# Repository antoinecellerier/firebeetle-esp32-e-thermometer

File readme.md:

A low power ESP32 based thermometer with an ePaper display

| Prototype | Custom board |
|-----------|--------------|
|||

See [docs/wiring.md](docs/wiring.md) for prototype wiring information and [hardware/thermometer-c6/](hardware/thermometer-c6/README.md) for the custom board. More pictures [lower down](#prototypes-in-action).

# Power consumption

Measured with a Nordic PPK2 on pure ESP-IDF firmware; full traces, dates and
methodology in [docs/notes.md](docs/notes.md). Figures are config-specific —
panel, sensor and board all matter.

**Read the node tag on every figure.** `@3V3 rail` is the load alone, with the
board's input tree bypassed; `@4V2 bat` is the whole deployment path, regulator
and charger leakage included. They are not interchangeable, and the battery
figure is not simply the larger one.

| Setup | Deep-sleep floor | Sensor wake | Wake + refresh |
|-------|-----------------|-------------|----------------|
| Firebeetle ESP32-E + BMP390L + GDEH0154Z90 via DESPI-C02 (FDN340P gate) | 19–20 µA `@3V3 rail` | ULP bit-bang I2C every 5 s, avg ≈0 | ~112 mC `@3V3 rail` (was ~600 mC before light sleep — the Z90's ~21 s refresh used to spin-wait) |
| XIAO ESP32-C6 + BMP581 + GDEH0576T81 via DESPI-C02 (FDN340P gate) | 15.5–16 µA `@3V3 rail` | LP core I2C every 60 s: ~1 mA × 3 ms | ~45 mC `@3V3 rail` — **superseded, re-measure** (see below) |
| XIAO ESP32-C6 + BMP581 + GDEW029I6FD via Seeed ePaper Driver Board (no gate) | ~25 µA `@3V3 rail`<br>**21.7 µA `@4V2 bat`** | LP core I2C every 60 s: ~1 mA × 3 ms | 12.2 mC `@3V3 rail`<br>**10.05 mC `@4V2 bat`** |
| thermometer-c6 rev A + BMP581 + GDEM0154I61 (on-board gated booster) | **18.3 µA `@4V2 bat`** | LP core I2C every 60 s | **~24.3 mC `@4V2 bat`** |
| thermometer-c6 rev A + BMP581 + GDEH0576T81 (on-board gated booster) | **19.05 µA `@4V2 bat`** | LP core I2C every 60 s | **36.77 mC `@4V2 bat`** |

The XIAO's GDEH0576T81 figure is **superseded**: it was taken while the panel ran
its coldest waveform LUT, which cost 48% of panel busy time. The last row is the
deployment configuration on the corrected waveform — daily budget and derivation
in [docs/notes.md](docs/notes.md).

A buck draws *less* current at 4.2 V than its load does at 3.3 V, which is why
~25 µA at the rail reads 21.7 µA at the battery (~90 % efficient). An LDO runs
the other way, ~1.15× the charge for the same work — so the custom board beating
the XIAO by 3 µA at the same 4.2 V is a real win, not a topology artefact. Its
wake figures include LED blinks, left on for observability. Blank cells are
unmeasured, not zero; both are on the PPK2 backlog.

The main CPU only wakes on a ≥0.1 °C delta or a safety-net tick, so a display
refresh is the dominant event on a typical day. At one refresh per hour that puts
long-term averages in the **~16–51 µA band depending on rig and refresh cadence**
— load-only runtime of roughly **1–3 years on a 400 mAh LiPo**, with the
deployment configuration measured at the bottom of that band (~2.3–3.8 C/day,
~380–620 days; derivation in [docs/notes.md](docs/notes.md)). But at this
current level LiPo self-discharge (a few %/month ≈ 15–25 µA equivalent) rivals
the load itself, so **expected runtime is on the order of a year**, and a
2600 mAh 18650 will age out before the load meaningfully drains it. Not yet
confirmed against a full-length run.

Two gotchas worth surfacing (the adapter-leakage ones are under Hardware below):
- **XIAO ESP32-C6 battery operation has a hard floor at ~3.6 V**: its 3.3 V rail is a pure buck (SGM6029C), which below VOUT + ~245 mV starves its bootstrap and lets the rail sag ~a VTH below VBAT — deep sleep survives, but wakes collapse into 0.5–0.9 A brownout-restart storms. Firmware shuts down at 3.7 V (~12–15 % of Li-ion capacity abandoned); full regime map in [docs/notes.md](docs/notes.md). LiFePO₄ cells (3.2 V nominal) are unusable on this board. The custom board uses an LDO and shuts down at 3.5 V instead.
- **Don't use the Seeed ePaper Driver Board's JST battery connector**: its ETA9740 charger/boost idles at ~330–500 µA — ~20× the whole system's sleep floor, flattening a 400 mAh cell in ~7 weeks doing nothing — and it double-converts BAT→5 V→3.3 V. Solder the battery to the XIAO's underside BAT pads instead, JST empty, switch off.

The Arduino-era ~20 mA deep-sleep USB CDC gotcha is gone: the pure-IDF
USB-Serial-JTAG console doesn't hold the port active.

For context: the original 2021 prototype (wake + refresh every 60 s, no ULP) ran a 2600 mAh cell flat in 8.5 days at ~12.6 mA average — the ULP/LP-core redesign is ~700× more efficient.

# Hardware

Looking to replicate this? Easy to start with options are tagged **[start with this]** below.

## Controller boards
- thermometer-c6 — the custom board this project builds towards, replacing the
  dev-board rigs below: ESP32-C6-MINI-1 + BMP581, a universal 24-pin FPC panel
  interface with the Good Display booster on-board and P-FET-gated, USB-C charging,
  an LDO 3.3 V rail, a GPIO-switched battery divider and a 32.768 kHz crystal.
  Schematic, PCB and rationale: [hardware/thermometer-c6/](hardware/thermometer-c6/README.md)
- Seeed Studio XIAO ESP32-C6 https://wiki.seeedstudio.com/xiao_esp32c6_getting_started/ **[start with this]**
- (Early 2021 prototype) Firebeetle ESP32-E https://wiki.dfrobot.com/FireBeetle_Board_ESP32_E_SKU_DFR0654
  - ESP32 datasheet https://www.espressif.com/sites/default/files/documentation/esp32_datasheet_en.pdf
  - ESP32-WROOM-32E datasheet  https://www.espressif.com/sites/default/files/documentation/esp32-wroom-32e_esp32-wroom-32ue_datasheet_en.pdf
  - TP4056 battery charger IC (onboard) https://dlnmh9ip6v2uc.cloudfront.net/datasheets/Prototyping/TP4056.pdf https://www.best-microcontroller-projects.com/tp4056.html

- ESP32 getting started https://docs.espressif.com/projects/esp-idf/en/latest/esp32/get-started/index.html
- ESP32 power consumption https://diyi0t.com/reduce-the-esp32-power-consumption/

## Temperature sensor (multiple options)
- BMP390L I2C interface:
  - datasheet https://www.bosch-sensortec.com/media/boschsensortec/downloads/datasheets/bst-bmp390-ds002.pdf
  - breakout board https://wiki.dfrobot.com/Fermion_BMP390L_Digital_Barometric_Pressure_Sensor_SKU_SEN0423
- BMP581 / BMP585 I2C interface (Bosch next-gen pressure sensors, ~0.5 µA deep-standby)
  - BMP581 https://www.bosch-sensortec.com/products/pressure-sensors/bmp581/
  - BMP585 https://www.bosch-sensortec.com/products/pressure-sensors/bmp585/
  - Fermion breakouts:
    - SEN0667 (BMP581) https://wiki.dfrobot.com/sen0667/ **[start with this]**
    - SEN0666 (BMP585) https://wiki.dfrobot.com/sen0666/
- (Early 2021 prototype) DS18B20-PAR OneWire interface
  - datasheet https://datasheets.maximintegrated.com/en/ds/DS18B20-PAR.pdf

## Display (multiple options)
- Good Display GDEW0154M09 black and white, 200x200, 1.54" fast full refresh https://www.good-display.com/product/206.html
- Good Display GDEW0213M21 black and white, 212x104, 2.13" DES screen https://www.good-display.com/product/354.html
- Good Display GDEW029I6FD black and white flex, 296x128, 2.9" (UC8151D, partial updates) https://www.good-display.com/product/209.html
- Good Display GDEM0154I61 black and white flex, 200x200, 1.54" (driven via GDEY0154D67 SSD1681 driver) https://www.good-display.com/product/535.html
- Good Display GDEH0576T81 black and white, 920x680, 5.76" HD (SSD2677, partial updates) https://www.good-display.com/product/702.html **[start with this]**
- (Early 2021 prototype) Adafruit 1.54" Tri-Color eInk / ePaper 200x200 Display with SRAM - SSD1681 Driver
https://www.adafruit.com/product/4868
https://learn.adafruit.com/adafruit-1-54-eink-display-breakouts?view=all
  - uses Good Display GDEH0154Z90 https://www.good-display.com/product/285.html

Good Display panels are driven through one of two adapters (same Good Display reference booster on both — panel compatibility notes in [docs/wiring.md](docs/wiring.md)):
- Good Display DESPI-C02 (switchable RESE 0.47/3 Ω) https://www.good-display.com/product/516.html
- Seeed ePaper Driver Board for XIAO (fixed RESE 0.47 Ω, ETA9740 charger — see gotcha above) https://www.seeedstudio.com/ePaper-breakout-Board-for-XIAO-V2-p-6374.html — wiki: https://wiki.seeedstudio.com/xiao_eink_expansion_board_v2/ **[start with this]**

The DESPI-C02's boost converter leaks ~534 µA in deep sleep, which an FDN340P P-channel MOSFET on the adapter's 3.3 V line eliminates; the Seeed board's ungated standby measured only ~9 µA, so it runs without a gate.

## Other components
- FDN340P P-channel MOSFET (SOT-23) — power-gates DESPI-C02 3.3 V during deep sleep
- AO3400A N-channel MOSFET (SOT-23) — switches the XIAO C6 battery voltage divider so it doesn't draw ~10 µA continuously

## Battery
- Current builds: PR502535 single-cell LiPo pouch, 400 mAh https://www.gotronic.fr/art-accu-lipo-3-7-vcc-400-mah-pr502535-5812.htm **[start with this or equivalent]**
- Original prototype: RS Pro 18650 26H Li-ion, 2600 mAh https://fr.rs-online.com/web/p/batteries-taille-speciale/1449406/

## Prototypes in action

### 2026 - ultra low power custom board

Custom rev A board (with BMP581), GDEM0154I61 & 400mAh battery

Custom rev A boards (with BMP581), GDEH0576T81 & 400mAh battery

### 2026 - ultra low power prototypes

Seed Xiao C6, BMP581, GDEH0576T81 & 400mAh battery

Seeed Xiao C6, e-Paper Driver Board, BMP581, GDEW029I6FD & 400mAh battery

Firebeetle ESP32-E, BMP390L, GDEH0154Z90 & 400mAh battery

### 2021 - first prototype
Firebeetle ESP32-E, DS18B20, GDEW0213M21 & 2600mAh battery

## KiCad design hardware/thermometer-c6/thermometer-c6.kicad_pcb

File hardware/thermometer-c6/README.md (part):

# thermometer-c6 — custom ultra-low-power e-paper thermometer board

Custom PCB replacing the XIAO-C6/FireBeetle dev-board rigs. ESP32-C6-MINI-1 +
BMP581 + universal 24-pin EPD interface with on-board gated booster, USB-C
charging, LDO power tree. Design driven by the PPK2 measurement campaign in
[`docs/notes.md`](../../docs/notes.md) (repo root).

**Status: rev A built and working.** Ordered 2026-07-20
([`archive/order-2026-07-20/`](archive/order-2026-07-20/); landed €273.93 ≈
€68.50/assembled board, breakdown in [`ORDERING.md`](ORDERING.md)). Board 1
passed bring-up Phases 0–2 on 2026-07-29 ([`BRINGUP.md`](BRINGUP.md)): first
render, LP-core survival, and a measured 18.3µA @ 4.2V deployment-path sleep
floor over a full field interval (docs/notes.md 2026-07-29) — vs 21.7µA at
the same 4.2V on the XIAO buck rig, validating the LDO tree. **Phase 3 is under
way on board 2, not board 1**: the GDEH0576T81 panels arrived 2026-08-11 and
board 2 took one plus a battery, so the phase is no longer gated on board 1
leaving its soak (still running since 2026-07-31; harvest before resetting it).
Closed on board 2 that day: the deployment configuration's power figures
(19.05µA floor, 36.77mC wake+refresh `@4V2 bat`), the boost rails under the
heaviest waveform the panel can be given (no sag — this is the evidence the
rev B bridge deletion was waiting on), the VBAT_ADC point (−24mV at 4.2V, 2mV
from board 1), the battery-floor sweep, and the WiFi resync charges. Board 2
went straight to flash on the strength of board 1's pass, worked first time,
and is both the bench board and now the Phase 3 vehicle; boards 3–4 are still
in the bag. The board is 48×35mm
2-layer, hand-routed, DRC-clean at full severity; fab export is `make fab`
(gerbers/drill + CPL/BOM zip, git-hash+date stamped, gated by
`verify/check_fab.py`); pre-order schematic sign-off (requirements proven
against primary sources, findings + dispositions):
[`SCHEMATIC-VERIFICATION.md`](SCHEMATIC-VERIFICATION.md).

## Why these choices (measurement rationale)

| Decision | Measurement behind it |
|---|---|
| LDO (not buck) 3.3V rail | XIAO's SGM6029C buck: razor-sharp dropout cliff at 3.545V → 0.5–0.9A brownout storms; forces 3.70V firmware shutdown, wasting ~12–15% of pack (notes.md 2026-07-05) |
| P-FET-gated EPD booster | DESPI-C02 leaks ~534µA with panel asleep; FDN340P gate mod → ~18µA (notes.md) |
| Switched 100k/100k battery divider | Always-on 200k divider ≈ 10µA (~⅔ of the sleep floor); 1M/1M biases the C6 SAR ADC low (~300ns sample window) (wiring.md) |
| High-side divider switch | Low-side switch leaves the sense node at VBAT through the top 100k → pin ESD diode clamps into 3V3 above ~3.7V (~5µA at 4.2V) |
| Load-sharing USB path | Without it, no-battery USB operation is limited to the 100mA charge current — EPD refresh peaks at ~465mA |
| Reverse-battery P-FET (Q6) | JST vs Adafruit pigtail polarity is a real supply-chain trap; MCP73831 abs-max is −0.3V — one AO3401A makes it survivable |
| EPD gate soft-start (R24/C28) | GPIO14 slamming Q2 on charge-shares 10µF against the rail faster than the LDO loop — ~100µs ramp kills the brownout risk |
| VBUS sense (R22/R23 → GPIO4) | Firmware needs to know USB is present: VBAT_ADC reads the charger CV node while charging, and SoC logic must ignore it; zero draw with USB absent |
| Jumper-selected inductor (JP5/JP6) | 10µH proven on all panels; 47µH per the GDEH0576T81 datasheet (with 2.2Ω RESE) — jumpers sit on the switch-node side so the unselected coil idles on the DC rail |
| 32.768kHz crystal | C6 on internal RC runs hours fast over weeks (memory: project_c6_clock_drift) |

## Reference transcription: DESPI-C02 V1.0 (Good Display, 2018-07-06)

Transcribed from `hardware/DESPI-C02_SCH V1.0.pdf` (visual + embedded netlist),
2026-07-07. This is the booster we replicate (with EPD_VCC gating added).

### 24-pin 0.5mm FPC panel pinout (P1, "FPC24(0.5MM)")

| Pin | Name | DESPI connection | Pin | Name | DESPI connection |
|---|---|---|---|---|---|
| 1 | NC | — | 13 | SCLK | host SPI SCK |
| 2 | GDR | Q1 gate + R1 10k→GND | 14 | SDI | host SPI MOSI |
| 3 | RESE | Q1 source + Rsense→GND | 15 | VDDIO | 3.3V |
| 4 | VGL | C1 4.7µF/25V→GND | 16 | VCI | 3.3V |
| 5 | VGH | C2 4.7µF/25V→GND | 17 | VSS | GND |
| 6 | TSCL | — (touch variant only) | 18 | VDD | C7 1µF/50V→GND |
| 7 | TSDA | — (touch variant only) | 19 | VPP | C8 1µF/50V→GND |
| 8 | BS | R4 3Ω→GND (= tied low, 4-wire SPI) | 20 | VSH | C9 4.7µF/25V→GND |
| 9 | BUSY | host | 21 | PREVGH | C5 4.7µF/25V→GND + D3 cathode |
| 10 | RES | host + R5 10k→3.3V pull-up | 22 | VSL | C10 4.7µF/25V→GND |
| 11 | D/C | host | 23 | PREVGL | C11 4.7µF/25V→GND + D1 anode |
| 12 | CS | host | 24 | VCOM | C12 1µF/50V→GND |

### Booster topology (all diodes MBR0530; orientation by function, not pin #)

- L1 10µH/1A: 3.3V → SW node
- Q1 Si1308EDL N-FET: gate=GDR (R1 10k bleed to GND), drain=SW, source=RESE
- RESE → Rsense → GND. DESPI: slide switch selects R3 0.47Ω or R2 3Ω.
  **This board: three parallel legs, each Rsense in series with a solder
  jumper: 0.47Ω (default-bridged) / 2.2Ω / 3Ω.**
- D3: anode=SW, cathode=PREVGH (boost rectifier)
- Negative charge pump: SW → C3 4.7µF/25V → X node; D2 anode=X, cathode=GND;
  D1 anode=PREVGL, cathode=X
- 3.3V rail bulk: C4 4.7µF/25V. (On this board the whole block hangs off the
  gated EPD_VCC rail, and the RES pull-up goes to EPD_VCC — never 3V3.)
- There are **no** PREVGH↔PREVGL/VCOM bridge caps in the real reference
  (the abandoned draft in `hardware/kicad/` invented them).

## ESP32-C6 pin map

| GPIO | Function | Notes |
|---|---|---|
| 0 / 1 | XTAL_32K_P / N | FC-135 32.768kHz + 20pF; R9 10M bias DNP — the C6's 32k oscillator amplifier runs at very low gm, so startup margin depends on crystal ESR spread (≤70kΩ allowed, rises when cold) and stray C; the parallel bias resistor (Espressif HDG checklist) gives the inverter a DC feedback path if a given board/batch won't start |
| 2 | VBAT_ADC (ADC1_CH2) | sense node of switched divider; 0V when divider off |
| 3 | VDIV_EN | 100k pull-down → divider hard-off in deep sleep |
| 4 | VBUS_SENSE (100k/100k from VBUS) | USB-presence detect; divider is dead (0V, zero drain) with USB unplugged |
| 5 | spare → J5 debug header | strap-adjacent (SDIO clock-edge only at default eFuses) — keep high-Z |
| 6 / 7 | LP I2C SDA / SCL | fixed by silicon; BMP581; 4.7k pull-ups to 3V3 |
| 8 | spare → J5 | STRAP: must be free to pull high for download boot — header only |
| 9 | BOOT button | strap, its intended use; 10k pull-up |
| 12 / 13 | USB D− / D+ | native USB-Serial-JTAG via USBLC6-2SC6 |
| 14 | EPD_PWR_EN (P-FET gate) | chosen because it is NOT in the SDIO strap group (GPIO18–23 can toggle during early boot, esp-idf #11975); 10k pull-up → panel off at reset/sleep |
| 15 | Status LED | safe: JTAG_SEL strap ignored at default eFuses |
| 16 / 17 | UART0 TX / RX → J5 | module pins TXD0/RXD0 |
| 18–21 | EPD MOSI/SCK/CS/DC | SDIO-group boot toggles drive an unpowered panel — harmless |
| 22 | EPD RST | 10k pull-up to **EPD_VCC** (gated) |
| 23 | EPD BUSY (input) | |

## Debug header J5 (2×5, DNP — GND-first, no VBAT)

The silk carries only a `DBG` marker (no room for a per-pin legend at ≥0.8mm),
so the pinout lives here. Standard 2×5 numbering, pin 1 = the marked corner:

| Pin | Signal | | Pin | Signal |
|---|---|---|---|---|
| 1 | GND | | 2 | +3V3 |
| 3 | EN (reset) | | 4 | DBG_TX (UART0 TXD0, GPIO16) |
| 5 | DBG_RX (UART0 RXD0, GPIO17) | | 6 | VBUS_SENSE (GPIO4) |
| 7 | DBG_IO5 (spare GPIO5) | | 8 | DBG_IO8 (spare GPIO8, strap) |
| 9 | GND | | 10 | GND |

DNP by default — solder a header only if you need wired debug/UART. **BOOT is
not on J5** (it's the SW2 button only); only EN is exposed here.

## Charging rule (product decision, 2026-07-07)

**Charge indoors only (0–45°C).** The MCP73831 has no thermistor input;
charging LiPo below 0°C plates lithium. The board carries this on back silk
(`CHARGE INDOORS 0-45°C`). Related: don't leave USB permanently attached — the
charger float-cycles the cell between ~3.95V and 4.2V indefinitely.
Firmware should also refuse to advertise "charge OK" below 0°C using the
BMP58x temperature (belt and braces; it cannot stop the charger).

## Inductor solder jumpers (JP5/JP6) — bridge exactly one

| Bridge | L | Pair with |
|---|---|---|
| JP5 (default) | L1 10µH | RESE 0.47Ω or 3Ω — the proven DESPI-C02 config for all six panels |
| JP6 | L2 47µH | RESE 2.2Ω (JP3) — the GDEH0576T81 datasheet booster spec |

## RESE solder jumpers (JP2/JP3/JP4) — bridge exactly one

| Bridge | Rsense | Panel family |
|---|---|---|
| JP2 (default) | 0.47Ω | GDEW/GDEY (UC81xx): GDEW0154M09, GDEW0213M21, GDEW029I6FD, GDEM0154I61; proven with GDEH0576T81 too (DESPI-C02 heritage) |
| JP3 | 2.2Ω | GDEH0576T81 per its datasheet (bridge JP6 to select L2 47µH with it) |
| JP4 | 3Ω | GDEH/GDEM SSD16xx: GDEH0154Z90 (tri-color), GDEH0154D67, GDEH0213B73, GDEH029A1 |

## Bench procedures

- **PPK2 source-mode power, deployment path (used for all published board-1
  figures)**: feed J1 through a Dupont-into-JST harness, JP1 untouched. Q6
  and the MCP73831 VBAT-pin leakage are in the measurement by construction —
  true battery-terminal figures. `tools/ppk2.py` rail id: `reva-j1` (also
  what `ppk2.py sweep` sweeps for the battery-floor regime map).
- **IBAT break — battery-current (series) measurement**: cut JP1 open and
  insert a PPK2 (or any ammeter) across J2 (the 2-pin header silk-labelled
  `IBAT`, DNP by default — solder one in). Battery in JST as usual. JP1
  ships as a factory copper bridge: knife-cut it the first time, re-close
  with solder afterwards (wicking only applies to a soldered re-bridge).
- **PPK2 source-mode at J2**: feed J2 pin 2 + GND, JST empty, JP1 open.
  Pin 2 is VBAT — the charger output node, not VSYS (VSYS has no TP or
  header; probe D2's cathode pad). Powers the LDO tree + charger but
  excludes Q6. `tools/ppk2.py` rail id: `reva-j2`.
- **Do NOT back-feed the 3V3 test pad**: RT9080 abs-max forbids VOUT > VIN
  + 0.3V, and its EN=0 active-discharge (~80Ω) would fight the source.
  TP4 (3V3) is probe-only.
- Charge current: R3 10k → 100mA (0.25C for a 400–500mAh pouch). 4.99k →
  200mA if a bigger pack is fitted.
- C29 (10nF ADC reservoir on VBAT_ADC) is populated by default: enable the
  divider ~5ms before reading (τ = 50k × 10n = 0.5ms).
- BMP58x INT pins are unconnected: firmware must configure int_en=1,
  int_od=0, pad_int_drv=0 per the Bosch datasheets.
- Battery thresholds are board-scoped in Thermometer.cpp: **3550 warn /
  3500mV shutdown** (applied 2026-07-31 from the sweep + BOD-probe
  measurements, notes.md 2026-07-30 — droop at the refresh peak ≈300mV, so
  3500 keeps ~200mV of rail margin over the C6's 3.0V spec floor). That
  recovers most of the ~25% of pack capacity the buck-era 3700mV cutoff
  stranded; the cold and real-cell BOD-probe runs decide whether 3450
  (~5-8% more, OCV estimate) is safe.
- The first-article measurement list lives in [`BRINGUP.md`](BRINGUP.md)
  Phase 3 (VGH/VGL spec at refresh, EPD_VCC soft-start ramp, 3V3 sag →
  threshold re-derivation, boost ILIM transient, 32k crystal cold start,
  SS14 warm-floor leakage, VBAT_ADC sweep, charging self-heat). The 32k crystal
  is proven running warm on board 1 (no RTC fallback warning); cold start
  remains open.
- While charging, the board self-heats slightly — BMP581 temperature reads
  high until it cools; log accordingly.

## BOM

Generated at `bom/thermometer-c6-bom.csv` (JLCPCB columns) from circuit.py.
Notable parts: ESP32-C6-MINI-1-N4 (C5736265), RT9080-33GJ5 (C841192),
MCP73831-2 (C424093), Si1308EDL (C469327, low stock — fallback Si1304BDL
clone C7419947), MBR0530 TWGMC (C5204746), FPC-05FB-24PH20 dual-contact
(C2856831), SWPA4030S100MT (C38117), FC-135 (C32346), BMP581 (C5362283 —
**restocked at LCSC as of 2026-07-17** (3,675 pcs); the fab BOM populates
U5 by default. Re-verify stock at order time like everything else).

DESPI-C02 §4.5 requires an FPC socket with "contact at up side or both
side" — hence the dual-contact FPC-05FB (the bottom-contact-only
FPC-05F-24PH20 C2856805 must NOT be substituted). **Rev B anti-regression
note — this became a measured requirement on 2026-08-11, not a paper one.**
The GDEH0576T81's FPC carries its contacts on the REAR face (away from the
screen); every other panel bench-tested here — GDEM0154I61, GDEY0213M21,
GDEH0154Z90, GDEW029I6FD — has them on the FRONT. A single-side socket would
therefore have worked on every panel used during bring-up and failed on the
one panel this board is being built for. It is exactly the line item a
cost-down pass reads as unnecessary margin; it is not. J4 uses the hand-drawn
`local:XUNPU_FPC-05FB-24PH20` footprint, transcribed from the XUNPU
FPC-05FB-NPH20 manufacture drawing (pads 0.3×1.2 @0.5mm, tabs 2.0×1.8 at
±7.3/+1.625 center-to-center) and cross-checked against the EasyEDA/JLC
C2856831 land pattern — the two agree exactly. The FPC-05FB is a rear-flip
connector: the SMT contact tails / pad row sit at the REAR (actuator) face,
and the mouth / cable entry is on the far side, 4.95mm from the pad centers
(body depth 5.40 = the XUNPU drawing; VERTEX_POINT-only STEP bbox,
`out/j3-land/` §7 2026-07-20 — the earlier 6.55 came from bounding-boxing
raw CARTESIAN_POINTs, which include LINE/AXIS2_PLACEMENT_3D entities that
own no geometry). On the board J4 is placed at rot 90 with the tail/pad
column WEST (x41.45) and the mouth EAST at x46.40, so the panel cable
approaches from the east edge. The mouth sits 1.60mm inboard of the edge
rather than flush — harmless for an FPC (the cable bottoms out inside the
housing either way) and it leaves the body fully supported. Pad 1 = panel circuit 1 sits at the NORTH end (the footprint pads are
numbered to keep pin 1 north despite the rear-flip geometry; the pin-1 silk
dot marks it). Pin-1 direction is verified against the DESPI-C02 manual
photos (P1 silk: "1" and "24" end markers, "24" at the P1-refdes end); note
the DESPI "P1" silk next to the pin-24 marker is the connector refdes, not
pin 1.

## Alternate sensor: BMP585 (U6, DNP by default)

The board carries footprints for BOTH BMP581 (U5, LGA-10 2×2) and BMP585
(U6, LGA-9 3.25×3.25, media-resistant — suitable for outdoor/weather-exposed
builds; gel-protected port under the metal lid, keep the Ø2.2mm opening
unobstructed in the enclosure). Same LP I2C bus, same 0x47 strapping
(CSB+SDO→VDDIO), same register map — the firmware BMP58x driver reads the
chip-ID (0x50=581, 0x51=585) and works with either unchanged.
**Populate exactly one**: both strap to address 0x47.
BMP585 = LCSC C18184976. Its datasheet
requires a 10Ω supply series resistor only for supply ramps <10µs — not
applicable here (always-on 3V3 rail, never GPIO-gated).

## Regenerating

```
make check   # generate + ERC + netlist golden check + invariants + footprints
make pdf     # out/thermometer-c6.pdf for review
```

The `.kicad_sch` is generated by `generator/generate.py` from
`generator/circuit.py` (nets/parts) + `generator/layout.py` (placement and
drawn wire routes) — edit those, never the .kicad_sch. Connectivity is
verified three ways: generator geometric checks (cross-net coincidence =
build error), `kicad-cli` ERC at zero tolerance, and exact netlist matching
against circuit.py (anonymous `~` nets matched by pin set).

## Open items (user sign-off) — all dispositioned

1. **BMP581 sourcing** — RESOLVED 2026-07-17: restocked at LCSC (3,675
   pcs); the ordered boards populate U5 BMP581. The BMP585 (C18184976)
   remains the U6 populate-one alternate (outdoor/media-resistant builds,
   or if the 581 dries up again).
2. **Si1308EDL stock thin** — RESOLVED by the order: C469327 is on the
   boards; the fallback Si1304BDL-clone C7419947 was never needed.
3. **Reverse-polarity protection** — RESOLVED: Q6 AO3401A P-FET at the
   JST is fitted (see "Why these choices"); a reversed cell is blocked,
   MCP73831's −0.3V abs-max is respected. Proven on board 1: body diode
   0.4259V diode-mode pass ([`BRINGUP.md`](BRINGUP.md) Phase 0). Keyed JST
   + silk remain the first line of defense.
4. **EPD SPI/control series resistors omitted** — CLOSED by construction,
   no veto: boards fabbed without them, firmware floats the pins when the
   panel is gated off (src/Display.cpp), first render passed on board 1.
   Disposition recorded in [`SCHEMATIC-VERIFICATION.md`](SCHEMATIC-VERIFICATION.md).
5. **JST-PH polarity** — RESOLVED 2026-07-29 on hardware: DMM on the loose
   plug, red wire / + contact mates with J1's `+`-marked pad
   ([`BRINGUP.md`](BRINGUP.md) Phase 0). JST vs Adafruit convention still
   differs — re-check any new pigtail.
6. **FPC footprint** — DONE and hardware-verified: hand-drawn
   `local:XUNPU_FPC-05FB-24PH20` (see BOM section), respun 2026-07-19
   after a numeric STEP proof (`out/j4-proof/`), body depth corrected to
   5.40 on 2026-07-20. Placement verified pre-order (75/75 placements,
   [`archive/order-2026-07-20/`](archive/order-2026-07-20/)); J4 pin-1 north
   / mouth-east confirmed by continuity on board 1
   ([`BRINGUP.md`](BRINGUP.md) Phase 0).
7. **32k crystal populated by default** — CONFIRMED: on the ordered boards
   and proven oscillating on board 1 (no RTC fallback warning in the boot
   log); cold start remains a [`BRINGUP.md`](BRINGUP.md) Phase 3 item.
8. **Old Copilot draft** — MOOT as originally written: `hardware/kicad/`
   was never merged and exists only on the unmerged branch
   `hardware/custom-esp32c6-pcb`. Nothing in the tree to delete; the
   remaining call is whether to delete that branch.

## Follow-up phases

- PCB layout (2-layer) — **DONE**: booster switch loop tight, RESE sense
  short, no-copper zone under BMP581, antenna keep-out per Espressif HDG,
  JLCPCB gerbers/drill + CPL/BOM via `make fab` (order per
  [`ORDERING.md`](ORDERING.md)).
- Firmware — **DONE**: `THERMOMETER_C6_BOARD` variant (`thermometer_c6_*`
  envs in platformio.ini): EPD on GPIO18–23 + gate GPIO14 with float-on-off,
  battery divider GPIO2/3, VBUS sense GPIO4 (suppresses SoC shutdown on USB),
  LED GPIO15, 32k crystal via `sdkconfig.defaults.thermometer_c6`.
- Fab order — **DONE** (2026-07-20,
  [`archive/order-2026-07-20/`](archive/order-2026-07-20/); landed cost
  breakdown in [`ORDERING.md`](ORDERING.md) §8).
- Bring-up Phases 0–2 — **DONE** on board 1 (2026-07-29,
  [`BRINGUP.md`](BRINGUP.md)); measured numbers in the
  [`docs/notes.md`](../../docs/notes.md) power logbook.
- **NEXT** (hardware): [`BRINGUP.md`](BRINGUP.md) Phase 3 first-article
  measurements. Board 1 has been on battery soak since 2026-07-31 and most of
  Phase 3 waits on it. Boards 3–4 need bringing up, but not the full Phase 0–1
  checklist — board 2 skipped it and worked; only board 4's flagged U5 skew
  wants the Phase 2 sensor detect run early.

## Routed-copper census (rev A final vs the pre-connector-fix board)

`python3 verify/copper_stats.py --vs 9100758` — baseline `9100758` is the last
commit before the J4 mouth-east respin, the J3 datum/land fork and the R2.2
corners. Tracks and vias only; pours are regenerated fill, not authored copper.

```
segments   977 ->  906     -71  (-7.3%)
vias       189 ->  154     -35 (-18.5%)
F.Cu mm  756.1 -> 643.5  -112.5 (-14.9%)
B.Cu mm  840.6 -> 736.2  -104.4 (-12.4%)
total   1596.6 ->1379.7  -216.9 (-13.6%)
nets shorter 40   longer 2   ~unchanged 18   (of 60)

vias by region   FPC/east x>36  36 -> 27      USB/north y<9  51 -> 28
                 west x<20      84 -> 72
```

Putting both connectors on their true datums made the board measurably
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
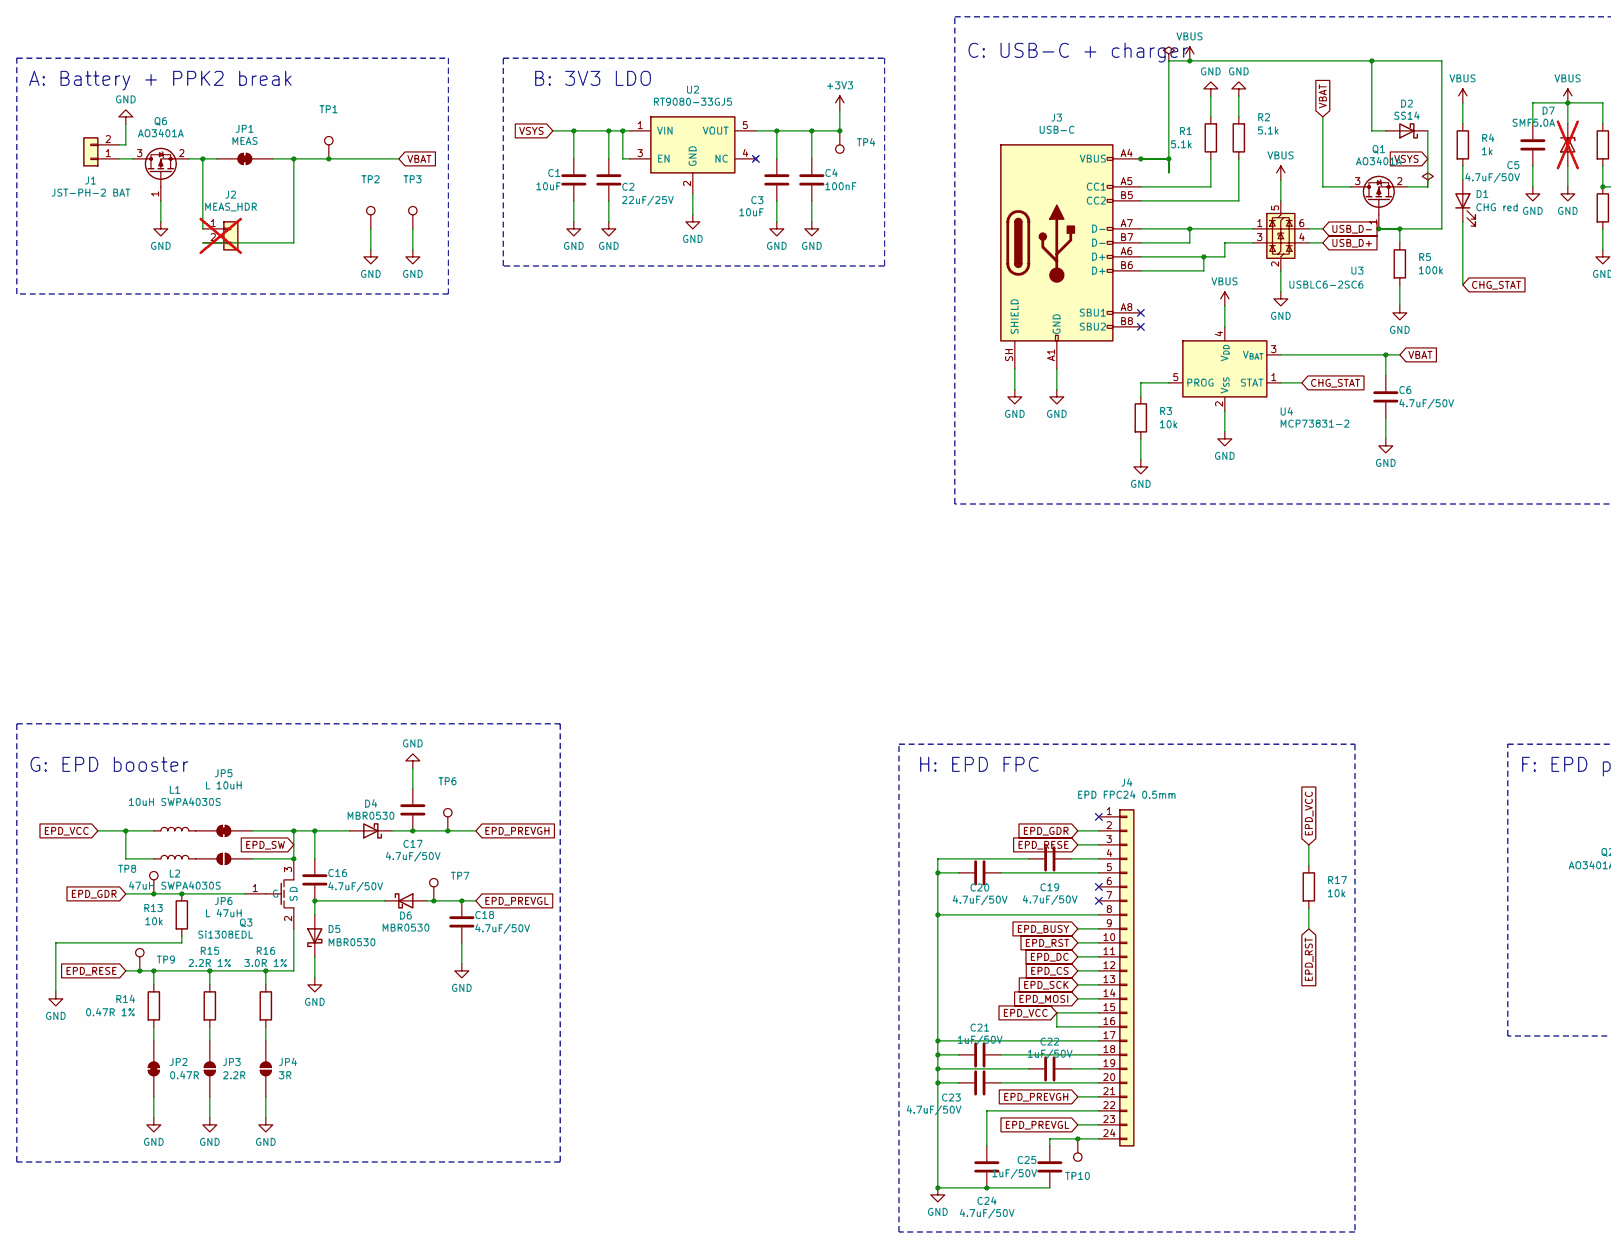
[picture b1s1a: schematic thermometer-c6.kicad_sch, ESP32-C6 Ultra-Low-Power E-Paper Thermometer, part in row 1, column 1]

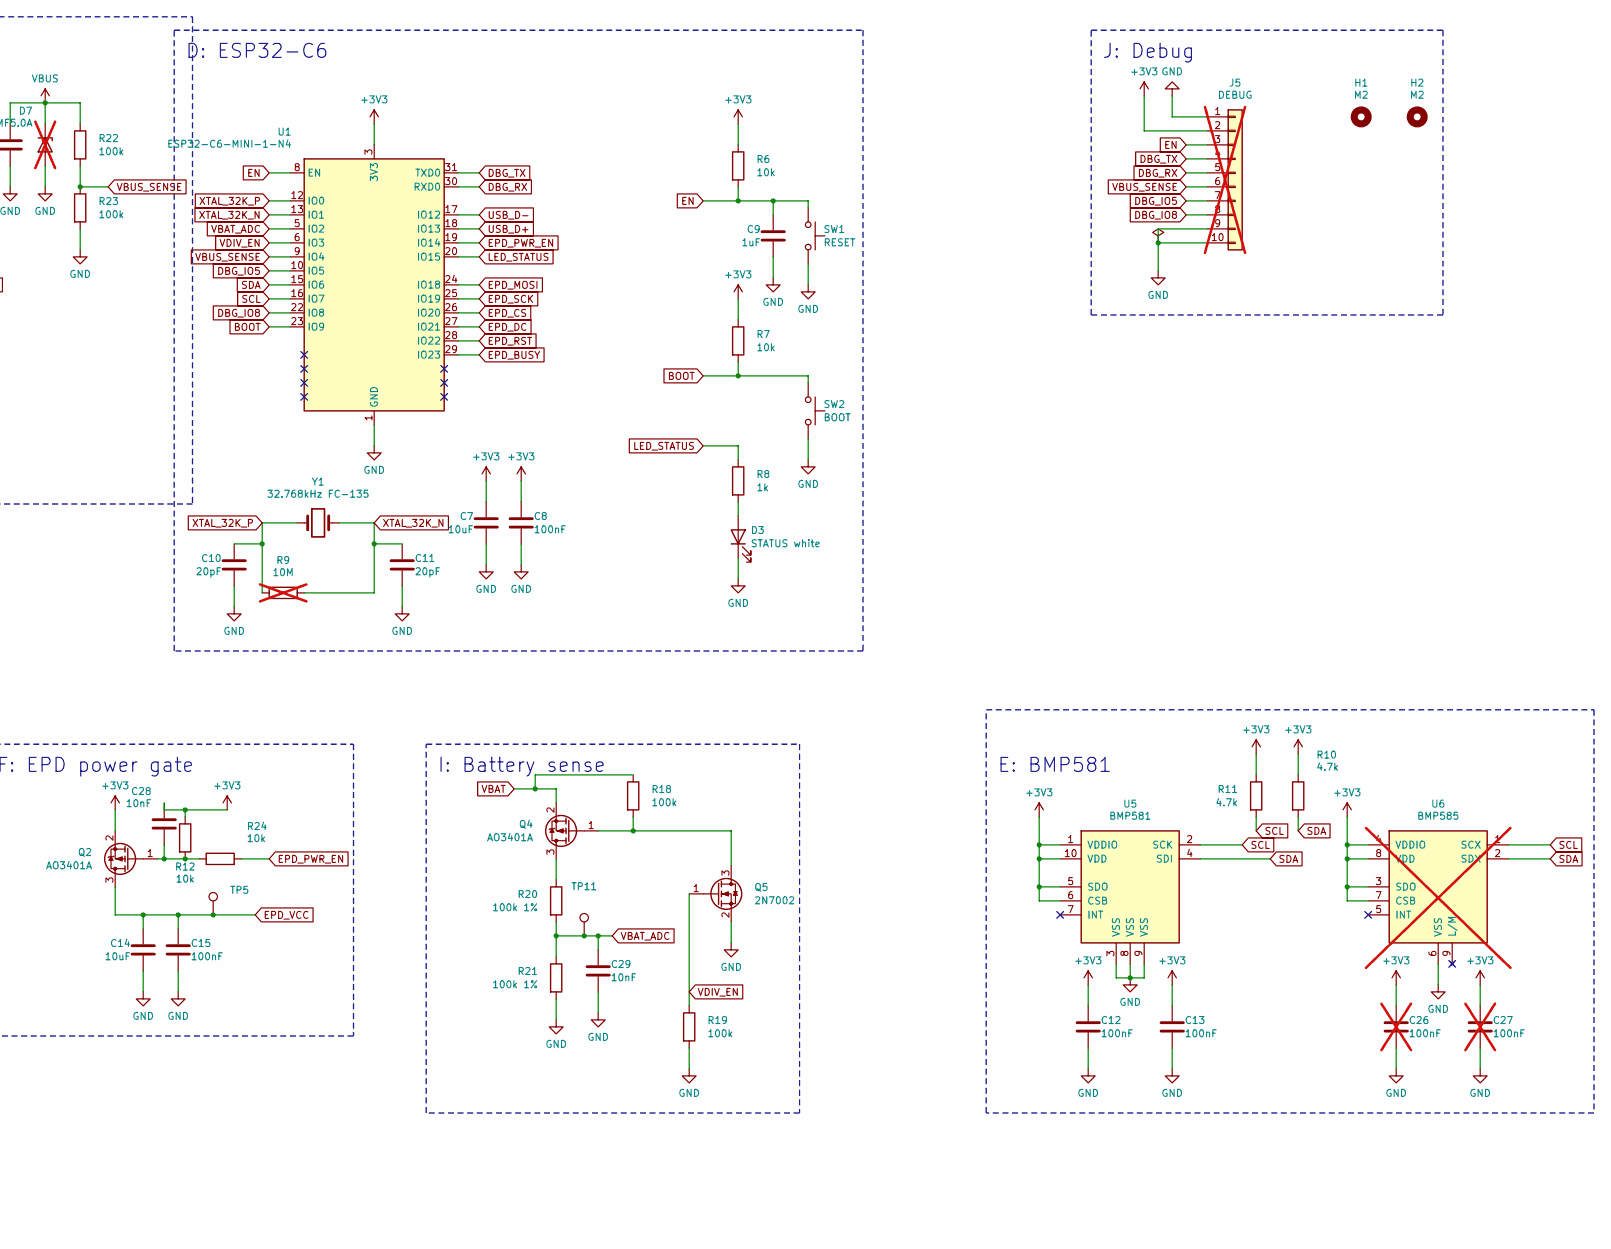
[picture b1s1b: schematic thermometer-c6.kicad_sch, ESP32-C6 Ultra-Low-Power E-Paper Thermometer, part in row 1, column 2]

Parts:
C1, C3, C7, C14: 10uF; C_0603_1608Metric; LCSC C19702
C2: 22uF/25V; C_0805_2012Metric; LCSC C45783
C4, C8, C12, C13, C15: 100nF; C_0402_1005Metric; LCSC C1525
C5, C6, C16, C17, C18, C19, C20, C23, C24: 4.7uF/50V; C_0805_2012Metric; LCSC C98192
C9: 1uF; C_0402_1005Metric; LCSC C52923
C10, C11: 20pF; C_0402_1005Metric; LCSC C1554
C21, C22, C25: 1uF/50V; C_0805_2012Metric; LCSC C28323
C26, C27: 100nF; C_0402_1005Metric; LCSC C1525; not fitted
C28, C29: 10nF; C_0402_1005Metric; LCSC C15195
D1: CHG red; LED_0603_1608Metric; LCSC C2286
D2: SS14; D_SMA; LCSC C2480
D3: STATUS white; LED_0603_1608Metric; LCSC C2290
D4, D5, D6: MBR0530; D_SOD-123; LCSC C5204746
D7: SMF5.0A; D_SOD-123F; not fitted
H1, H2: M2; MountingHole_2.2mm_M2
J1: JST-PH-2 BAT; JST_PH_S2B-PH-SM4-TB_1x02-1MP_P2.00mm_Horizontal; LCSC C295747
J2: MEAS_HDR; PinHeader_1x02_P2.54mm_Vertical; not fitted
J3: USB-C; USB_C_Receptacle_HRO_TYPE-C-31-M-12; LCSC C165948
J4: EPD FPC24 0.5mm; XUNPU_FPC-05FB-24PH20; LCSC C2856831
J5: DEBUG; PinHeader_2x05_P2.54mm_Vertical; not fitted
JP1: MEAS; SolderJumper-2_P1.3mm_Bridged_RoundedPad1.0x1.5mm
JP2: 0.47R; SolderJumper-2_P1.3mm_Bridged_RoundedPad1.0x1.5mm
JP3: 2.2R; SolderJumper-2_P1.3mm_Open_RoundedPad1.0x1.5mm
JP4: 3R; SolderJumper-2_P1.3mm_Open_RoundedPad1.0x1.5mm
JP5: L 10uH; SolderJumper-2_P1.3mm_Bridged_RoundedPad1.0x1.5mm
JP6: L 47uH; SolderJumper-2_P1.3mm_Open_RoundedPad1.0x1.5mm
L1: 10uH SWPA4030S; L_Sunlord_SWPA4030S; LCSC C38117
L2: 47uH SWPA4030S; L_Sunlord_SWPA4030S; LCSC C54731
Q1, Q2, Q4, Q6: AO3401A; SOT-23; LCSC C15127
Q3: Si1308EDL; SOT-323_SC-70; LCSC C469327
Q5: 2N7002; SOT-23; LCSC C8545
R1, R2: 5.1k; R_0402_1005Metric; LCSC C25905
R3, R6, R7, R12, R13, R17, R24: 10k; R_0402_1005Metric; LCSC C25744
R4, R8: 1k; R_0402_1005Metric; LCSC C11702
R5, R18, R19, R22, R23: 100k; R_0402_1005Metric; LCSC C25741
R9: 10M; R_0402_1005Metric; not fitted
R10, R11: 4.7k; R_0402_1005Metric; LCSC C25900
R14: 0.47R 1%; R_0805_2012Metric; LCSC C2930220
R15: 2.2R 1%; R_0805_2012Metric; LCSC C17521
R16: 3.0R 1%; R_0805_2012Metric; LCSC C17660
R20, R21: 100k 1%; R_0402_1005Metric; LCSC C25741
SW1: RESET; SW_TS-1187A; LCSC C318884
SW2: BOOT; SW_TS-1187A; LCSC C318884
TP1: VBAT; TestPoint_Pad_D1.5mm
TP2, TP3: GND; TestPoint_Pad_D1.5mm
TP4: 3V3; TestPoint_Pad_D1.5mm
TP5: EPD_VCC; TestPoint_Pad_D1.5mm
TP6: PREVGH; TestPoint_Pad_D1.5mm
TP7: PREVGL; TestPoint_Pad_D1.5mm
TP8: GDR; TestPoint_Pad_D1.5mm
TP9: RESE; TestPoint_Pad_D1.5mm
TP10: VCOM; TestPoint_Pad_D1.5mm
TP11: VBAT_ADC; TestPoint_Pad_D1.5mm
U1: ESP32-C6-MINI-1-N4; ESP32-C6-MINI-1; LCSC C5736265
U2: RT9080-33GJ5; TSOT-23-5; LCSC C841192
U3: USBLC6-2SC6; SOT-23-6; LCSC C7519
U4: MCP73831-2; SOT-23-5; LCSC C424093
U5: BMP581; Bosch_LGA-10_2x2mm; LCSC C5362283
U6: BMP585; Bosch_LGA-9_3.25x3.25mm; LCSC C18184976; not fitted
Y1: 32.768kHz FC-135; Crystal_SMD_3215-2Pin_3.2x1.5mm; LCSC C32346

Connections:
+3V3: C3.1, C4.1, C7.1, C8.1, C12.1, C13.1, C26.1, C27.1, C28.1, J5.2, Q2.2 (S), R6.1, R7.1, R10.1, R11.1, R12.1, TP4.1, U1.3 (3V3), U2.5 (VOUT), U5.1 (VDDIO), U5.5 (SDO), U5.6 (CSB), U5.10 (VDD), U6.3 (SDO), U6.4 (VDDIO), U6.7 (CSB), U6.8 (VDD)
BOOT: R7.2, SW2.1, U1.23 (IO9)
CHG_STAT: D1.1 (K), U4.1 (STAT)
DBG_IO5: J5.7, U1.10 (IO5)
DBG_IO8: J5.8, U1.22 (IO8)
DBG_RX: J5.5, U1.30 (RXD0)
DBG_TX: J5.4, U1.31 (TXD0)
EN: C9.1, J5.3, R6.2, SW1.1, U1.8 (EN)
EPD_BUSY: J4.9, U1.29 (IO23)
EPD_CS: J4.12, U1.26 (IO20)
EPD_DC: J4.11, U1.27 (IO21)
EPD_GDR: J4.2, Q3.1 (G), R13.1, TP8.1
EPD_MOSI: J4.14, U1.24 (IO18)
EPD_PREVGH: C17.1, D4.1 (K), J4.21, TP6.1
EPD_PREVGL: C18.1, D6.2 (A), J4.23, TP7.1
EPD_PWR_EN: R24.2, U1.19 (IO14)
EPD_RESE: J4.3, Q3.2 (S), R14.1, R15.1, R16.1, TP9.1
EPD_RST: J4.10, R17.2, U1.28 (IO22)
EPD_SCK: J4.13, U1.25 (IO19)
EPD_SW: C16.1, D4.2 (A), JP5.2 (B), JP6.2 (B), Q3.3 (D)
EPD_VCC: C14.1, C15.1, J4.15, J4.16, L1.1, L2.1, Q2.3 (D), R17.1, TP5.1
GND: C1.2, C2.2, C3.2, C4.2, C5.2, C6.2, C7.2, C8.2, C9.2, C10.2, C11.2, C12.2, C13.2, C14.2, C15.2, C17.2, C18.2, C19.2, C20.2, C21.2, C22.2, C23.2, C24.2, C25.2, C26.2, C27.2, C29.2, D3.1 (K), D5.1 (K), D7.2 (A), J1.2, J3.A1 (GND), J3.A12 (GND), J3.B1 (GND), J3.B12 (GND), J3.SH (SHIELD), J4.8, J4.17, J5.1, J5.9, J5.10, JP2.2 (B), JP3.2 (B), JP4.2 (B), Q5.2 (S), Q6.1 (G), R1.2, R2.2, R3.2, R5.2, R13.2, R19.2, R21.2, R23.2, SW1.2, SW2.2, TP2.1, TP3.1, U1.1 (GND), U1.2 (GND), U1.11 (GND), U1.14 (GND), U1.36 (GND), U1.37 (GND), U1.38 (GND), U1.39 (GND), U1.40 (GND), U1.41 (GND), U1.42 (GND), U1.43 (GND), U1.44 (GND), U1.45 (GND), U1.46 (GND), U1.47 (GND), U1.48 (GND), U1.49 (GND), U1.50 (GND), U1.51 (GND), U1.52 (GND), U1.53 (GND), U2.2 (GND), U3.2 (GND), U4.2 (V_{SS}), U5.3 (VSS), U5.8 (VSS), U5.9 (VSS), U6.6 (VSS)
LED_STATUS: R8.1, U1.20 (IO15)
unnamed: D1.2 (A), R4.2
unnamed: D3.2 (A), R8.2
unnamed: C16.2, D5.2 (A), D6.1 (K)
unnamed: J1.1, Q6.3 (D)
unnamed: J2.1, JP1.1 (A), Q6.2 (S)
unnamed: J3.A5 (CC1), R1.1
unnamed: J3.B5 (CC2), R2.1
unnamed: J3.A6 (D+), J3.B6 (D+), U3.3 (I/O2)
unnamed: J3.A7 (D-), J3.B7 (D-), U3.1 (I/O1)
unnamed: C19.1, J4.4
unnamed: C20.1, J4.5
unnamed: C21.1, J4.18
unnamed: C22.1, J4.19
unnamed: C23.1, J4.20
unnamed: C24.1, J4.22
unnamed: C25.1, J4.24, TP10.1
unnamed: JP2.1 (A), R14.2
unnamed: JP3.1 (A), R15.2
unnamed: JP4.1 (A), R16.2
unnamed: JP5.1 (A), L1.2
unnamed: JP6.1 (A), L2.2
unnamed: C28.2, Q2.1 (G), R12.2, R24.1
unnamed: Q4.3 (D), R20.1
unnamed: Q4.1 (G), Q5.3 (D), R18.2
unnamed: R3.1, U4.5 (PROG)
SCL: R11.2, U1.16 (IO7), U5.2 (SCK), U6.1 (SCX)
SDA: R10.2, U1.15 (IO6), U5.4 (SDI), U6.2 (SDX)
USB_D+: U1.18 (IO13), U3.4 (I/O2)
USB_D-: U1.17 (IO12), U3.6 (I/O1)
VBAT: C6.1, J2.2, JP1.2 (B), Q1.3 (D), Q4.2 (S), R18.1, TP1.1, U4.3 (V_{BAT})
VBAT_ADC: C29.1, R20.2, R21.1, TP11.1, U1.5 (IO2)
VBUS: C5.1, D2.2 (A), D7.1 (K), J3.A4 (VBUS), J3.A9 (VBUS), J3.B4 (VBUS), J3.B9 (VBUS), Q1.1 (G), R4.1, R5.1, R22.1, U3.5 (VBUS), U4.4 (V_{DD})
VBUS_SENSE: J5.6, R22.2, R23.1, U1.9 (IO4)
VDIV_EN: Q5.1 (G), R19.1, U1.6 (IO3)
VSYS: C1.1, C2.1, D2.1 (K), Q1.2 (S), U2.1 (VIN), U2.3 (EN)
XTAL_32K_N: C11.1, R9.2, U1.13 (IO1), Y1.2
XTAL_32K_P: C10.1, R9.1, U1.12 (IO0), Y1.1

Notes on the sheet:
A: Battery + PPK2 break
B: 3V3 LDO
C: USB-C + charger
D: ESP32-C6
J: Debug
G: EPD booster
H: EPD FPC
F: EPD power gate
I: Battery sense
E: BMP581

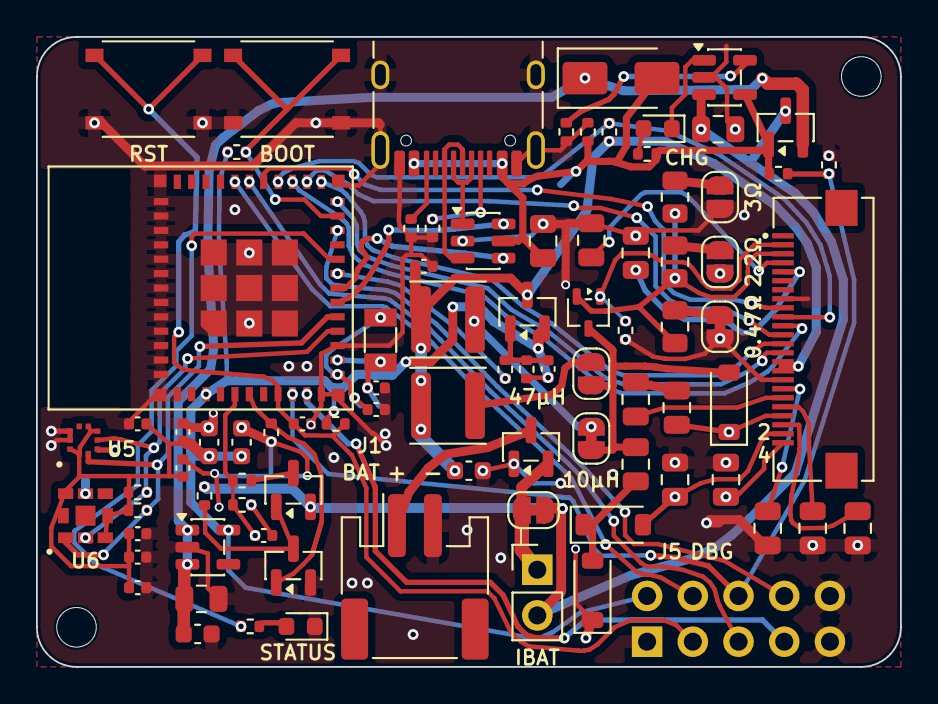
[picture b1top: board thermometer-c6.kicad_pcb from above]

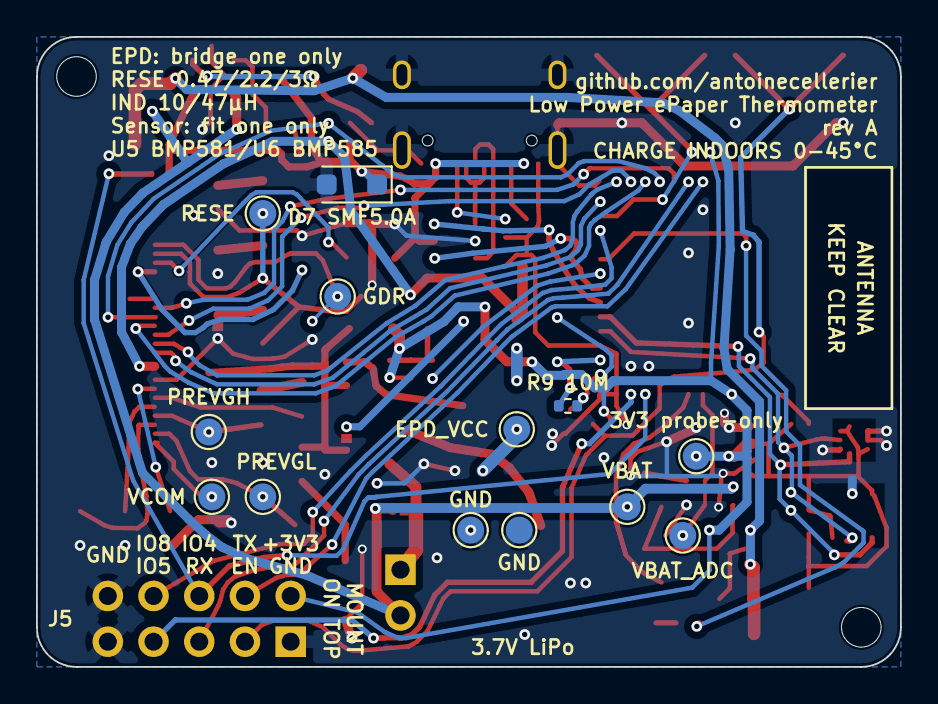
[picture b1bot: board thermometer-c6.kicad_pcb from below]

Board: 2 copper layers, 48.0 x 35.0 mm, 101 parts (13 on the bottom side), 60 nets.

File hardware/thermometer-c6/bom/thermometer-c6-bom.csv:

Comment,Designator,Footprint,LCSC Part #
10uF,"C1,C14,C3,C7",Capacitor_SMD:C_0603_1608Metric,C19702
20pF,"C10,C11",Capacitor_SMD:C_0402_1005Metric,C1554
22uF/25V,C2,Capacitor_SMD:C_0805_2012Metric,C45783
1uF/50V,"C21,C22,C25",Capacitor_SMD:C_0805_2012Metric,C28323
10nF,"C28,C29",Capacitor_SMD:C_0402_1005Metric,C15195
100nF,"C12,C13,C15,C4,C8",Capacitor_SMD:C_0402_1005Metric,C1525
4.7uF/50V,"C16,C17,C18,C19,C20,C23,C24,C5,C6",Capacitor_SMD:C_0805_2012Metric,C98192
1uF,C9,Capacitor_SMD:C_0402_1005Metric,C52923
CHG red,D1,LED_SMD:LED_0603_1608Metric,C2286
SS14,D2,Diode_SMD:D_SMA,C2480
STATUS white,D3,LED_SMD:LED_0603_1608Metric,C2290
MBR0530,"D4,D5,D6",Diode_SMD:D_SOD-123,C5204746
JST-PH-2 BAT,J1,Connector_JST:JST_PH_S2B-PH-SM4-TB_1x02-1MP_P2.00mm_Horizontal,C295747
USB-C,J3,Connector_USB:USB_C_Receptacle_HRO_TYPE-C-31-M-12,C165948
EPD FPC24 0.5mm,J4,local:XUNPU_FPC-05FB-24PH20,C2856831
10uH SWPA4030S,L1,Inductor_SMD:L_Sunlord_SWPA4030S,C38117
47uH SWPA4030S,L2,Inductor_SMD:L_Sunlord_SWPA4030S,C54731
Si1308EDL,Q3,Package_TO_SOT_SMD:SOT-323_SC-70,C469327
2N7002,Q5,Package_TO_SOT_SMD:SOT-23,C8545
AO3401A,"Q1,Q2,Q4,Q6",Package_TO_SOT_SMD:SOT-23,C15127
5.1k,"R1,R2",Resistor_SMD:R_0402_1005Metric,C25905
4.7k,"R10,R11",Resistor_SMD:R_0402_1005Metric,C25900
0.47R 1%,R14,Resistor_SMD:R_0805_2012Metric,C2930220
2.2R 1%,R15,Resistor_SMD:R_0805_2012Metric,C17521
3.0R 1%,R16,Resistor_SMD:R_0805_2012Metric,C17660
100k 1%,"R20,R21",Resistor_SMD:R_0402_1005Metric,C25741
10k,"R12,R13,R17,R24,R3,R6,R7",Resistor_SMD:R_0402_1005Metric,C25744
1k,"R4,R8",Resistor_SMD:R_0402_1005Metric,C11702
100k,"R18,R19,R22,R23,R5",Resistor_SMD:R_0402_1005Metric,C25741
RESET,SW1,local:SW_TS-1187A,C318884
BOOT,SW2,local:SW_TS-1187A,C318884
ESP32-C6-MINI-1-N4,U1,local:ESP32-C6-MINI-1,C5736265
RT9080-33GJ5,U2,Package_TO_SOT_SMD:TSOT-23-5,C841192
USBLC6-2SC6,U3,Package_TO_SOT_SMD:SOT-23-6,C7519
MCP73831-2,U4,Package_TO_SOT_SMD:SOT-23-5,C424093
BMP581,U5,local:Bosch_LGA-10_2x2mm,C5362283
32.768kHz FC-135,Y1,Crystal:Crystal_SMD_3215-2Pin_3.2x1.5mm,C32346

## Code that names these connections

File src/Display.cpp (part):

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
#if defined(ARDUINO_DFROBOT_FIREBEETLE_2_ESP32E)
// 3.3V GND SCK MOSI DC CS BUSY RESET pins are all on the same side of the Firebeetle board
#define EPD_DC     2 // D9
#define EPD_CS    14 // D6 (was D5/GPIO0, moved to free GPIO0 for RTC I2C SDA)
#define EPD_BUSY  26 // D3
#define EPD_RESET 25 // D2
#elif defined(ARDUINO_XIAO_ESP32C6)
#if defined(SEEED_XIAO_EPD_BOARD)
// Seeed ePaper Driver Board for XIAO — the shield hardwires these
// (SCK=D8/MOSI=D10 match the DESPI wiring; see docs/wiring.md)
#define EPD_DC    21 // D3
#define EPD_CS     1 // D1
#define EPD_BUSY   2 // D2
#define EPD_RESET  0 // D0
// The shield has no panel power gate (3V3 hardwired to booster/FPC), so
// override an EPD_POWER_GATE left enabled in local-secrets.h.
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#elif defined(THERMOMETER_C6_BOARD)
// Custom thermometer-c6 board (hardware/thermometer-c6): EPD deliberately on
// the SDIO strap group — boot-time toggles drive an unpowered (gated) panel.
#define EPD_DC    21
#define EPD_CS    20
#define EPD_BUSY  23
#define EPD_RESET 22 // 10k pull-up to gated EPD_VCC (not 3V3)
#ifndef EPD_POWER_GATE
#error "THERMOMETER_C6_BOARD requires EPD_POWER_GATE in local-secrets.h (the panel rail is hardware-gated)"
#endif
#else
// DESPI-C02, same Dx labels as Firebeetle — see docs/wiring.md for C6 GPIO mapping
#define EPD_DC    20 // D9
#define EPD_CS    16 // D6
#define EPD_BUSY  21 // D3
#define EPD_RESET  2 // D2
#endif
#else
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#if defined(ARDUINO_DFROBOT_FIREBEETLE_2_ESP32E)
#define EPD_POWER 13 // D7 — P-FET gate: LOW = on, HIGH = off
#elif defined(THERMOMETER_C6_BOARD)
#define EPD_POWER 14 // EPD_PWR_EN → Q2 P-FET via R24 soft-start; 10k pull-up = off at reset/sleep
#elif defined(ARDUINO_XIAO_ESP32C6)
#define EPD_POWER 17 // D7
#else
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  // its input protection diodes (CS and RST both idle high). Float the
  // plain-GPIO control pins — epd_configure_pins() re-arms them on next use.
  // MOSI/SCK stay bound to the SPI peripheral (idle low, harmless).
  const int pins[] = {EPD_CS, EPD_DC, EPD_RESET};
  for (size_t i = 0; i < sizeof(pins) / sizeof(pins[0]); i++)
  {
    gpio_set_direction((gpio_num_t)pins[i], GPIO_MODE_INPUT);
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  // Ensure EPD pins are in GPIO mode before GxEPD2 calls digitalWrite.
  // Required on C6 where GPIO16 (CS) defaults to non-GPIO function;
  // harmless on ESP32-E where these are already GPIO.
  pinMode(EPD_CS, OUTPUT);
  pinMode(EPD_DC, OUTPUT);
  pinMode(EPD_RESET, OUTPUT);
#if defined(ARDUINO_XIAO_ESP32C6)
  // GxEPD2 calls SPI.begin() with no args, which configures GPIO20 as MISO
  // and GPIO21 as SS — both conflict with EPD_DC and EPD_BUSY. Pre-init SPI
  // with only SCK/MOSI (e-paper is write-only, CS managed by GxEPD2).
  //
  // "Write-only" is this project's choice for SOME panels and a hardware fact for
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  SPI.begin(19 /* SCK, D8 */, -1, 18 /* MOSI, D10 */, -1);
  // Reconfigure DC and BUSY after SPI.begin() since it may have claimed them
  // as MISO/SS (GPIO20/21 are the default SPI MISO/SS on C6).
  pinMode(EPD_DC, OUTPUT);
  pinMode(EPD_BUSY, INPUT);
#else
  pinMode(EPD_BUSY, INPUT);
#endif
}

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
// SPI pins as wired (match components/arduino_shim/spi_shim.cpp defaults)
#if defined(ARDUINO_DFROBOT_FIREBEETLE_2_ESP32E)
#define EPD_SCK  18
#define EPD_MOSI 23
#elif defined(ARDUINO_XIAO_ESP32C6)
#define EPD_SCK  19
#define EPD_MOSI 18
#endif

// In light sleep, GPIOs switch to their per-pin sleep configuration — the EPD
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// glitches mid-refresh and aborts the waveform (symptom: faint noise, no image).
static void epd_pin_sleep_hold()
{
  const int pins[] = {EPD_CS, EPD_DC, EPD_RESET, EPD_SCK, EPD_MOSI,
#ifdef EPD_POWER_GATE
                      EPD_POWER, // FET gate must stay LOW (panel powered) through slices
#endif
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    sleep_ms(5);
    return;
  }
  int busy_level = gpio_get_level((gpio_num_t)EPD_BUSY);
  gpio_wakeup_enable((gpio_num_t)EPD_BUSY,
                     busy_level ? GPIO_INTR_LOW_LEVEL : GPIO_INTR_HIGH_LEVEL);
  esp_sleep_enable_gpio_wakeup();
  esp_sleep_enable_timer_wakeup(500000); // backstop only — the GPIO level wake ends each wait instantly
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#if SOC_PM_SUPPORT_TOP_PD
  esp_sleep_pd_config(ESP_PD_DOMAIN_TOP, ESP_PD_OPTION_AUTO);
#endif
  gpio_wakeup_disable((gpio_num_t)EPD_BUSY);
  esp_sleep_disable_wakeup_source(ESP_SLEEP_WAKEUP_GPIO);
  esp_sleep_disable_wakeup_source(ESP_SLEEP_WAKEUP_TIMER);
}
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static void epd_probe_read(uint8_t cmd, uint8_t *out, int n, bool pullup)
{
  SPI.end();
  pinMode(EPD_SCK, OUTPUT);
  digitalWrite(EPD_SCK, LOW);
  pinMode(EPD_MOSI, OUTPUT);

  digitalWrite(EPD_CS, LOW);
  digitalWrite(EPD_DC, LOW);                       // command phase
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  }

  digitalWrite(EPD_DC, HIGH);                      // data phase
  gpio_set_direction((gpio_num_t)EPD_MOSI, GPIO_MODE_INPUT);
  if (pullup)  { gpio_pullup_en((gpio_num_t)EPD_MOSI);  gpio_pulldown_dis((gpio_num_t)EPD_MOSI); }
  else         { gpio_pulldown_en((gpio_num_t)EPD_MOSI); gpio_pullup_dis((gpio_num_t)EPD_MOSI); }
  for (int b = 0; b < n; b++)
  {
    uint8_t v = 0;
    for (int i = 0; i < 8; i++)
    {
      digitalWrite(EPD_SCK, HIGH);
      v = (uint8_t)((v << 1) | (gpio_get_level((gpio_num_t)EPD_MOSI) ? 1 : 0));
      digitalWrite(EPD_SCK, LOW);
    }
    out[b] = v;
  }
  digitalWrite(EPD_CS, HIGH);
  gpio_pullup_dis((gpio_num_t)EPD_MOSI);
  gpio_pulldown_dis((gpio_num_t)EPD_MOSI);

  epd_configure_pins();  // restores SPI with explicit pins; a bare SPI.begin()
                         // would reclaim GPIO20/21 on the C6
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
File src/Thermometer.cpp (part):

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  // against a level that is already high fires immediately and forever. The
  // cable-already-in case is covered by the shortened safety net above instead.
  if (!vbus_present())
    app_enable_gpio_high_wakeup(VBUS_SENSE_GPIO);
#endif
  fflush(stdout);
  PPK2_CPU_ACTIVE_LOW();
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  return battery_mv;
#elif defined(THERMOMETER_C6_BOARD)
  // Custom thermometer-c6 board: high-side switched 100k/100k divider
  // (R20/R21). VDIV_EN (GPIO3) high → Q5 NFET → Q4 P-FET connects VBAT;
  // the external 100k pull-down keeps it hard-off in deep sleep. C29 10nF
  // reservoir on the ADC node charges through 100k — give it a few ms.
  // VBAT_ADC = GPIO2 = ADC1_CH2. While VBUS is present this node reads the
  // charger CV output, not battery SoC — see vbus_present().
  // ADC-failure fallback sits between no_battery_mv and low_battery_mv:
  // visible as a warning, can never trigger permanent shutdown.
  const uint32_t adc_fail_mv = 3525;

  gpio_out_init(3 /* VDIV_EN */);
  gpio_set_level(GPIO_NUM_3, 1);
  sleep_ms(5);

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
